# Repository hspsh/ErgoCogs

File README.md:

# ErgoCogs - modular ErgoDox for lifelong tinkerers

The idea for this project was born, when a couple of us couldn't decide on which features should our upcoming ErgoDox fork have.

The (conflicting) ideas were:
* Basic teensy with mini-usb
* Anything USB-C based
* Battery - powered bluetooth keyboard
* Custom STM32-based logic with SMD pre-assembly at factory

So why not have it all? The simplest solution is splitting the design into 2 parts. It has many advantages:

* The stupid matrix PCB is also the most expensive, as PCB manufacturers usually charge extra for anything larger than 10x10cm.
* If you get bored with with your basic bitch cherry mx matrix, why not swap it for them crunchy jade kalihs? Maybe just for a weekend? Or maybe sell your old matrix to a fellow hacker!
* The controller PCBs are small, and hence dirt cheap, and this is where most of customisation would take place. Take your time and experiment with wacky knobs and OLED displays until you get your perfect hackertyper experience.

It also has some disadvantages:

* The goldpin connector might be not the most relaiable way to connect 2PCBs. We're yet to check if this concept actually works out. Worst case, both sides may be semi-permanently soldered together with longer pinheaders.

## MatrixCog

This PCB is as dumb as it gets - it's basically an switch matrix routed do the 2x5 + 2x3 goldpin side connectors. It also features some LEDs.

To save some time, I recommend ordering this one with silicon diodes pre-assembled (`.cpl` file is included)

## BrainCogs

Here's when the fun begins. We provide 2 example hemispheres that feature some basic functionalities. You can fork the shit out of this repo and modify these for your own needs.

## Some pictures

More to come...

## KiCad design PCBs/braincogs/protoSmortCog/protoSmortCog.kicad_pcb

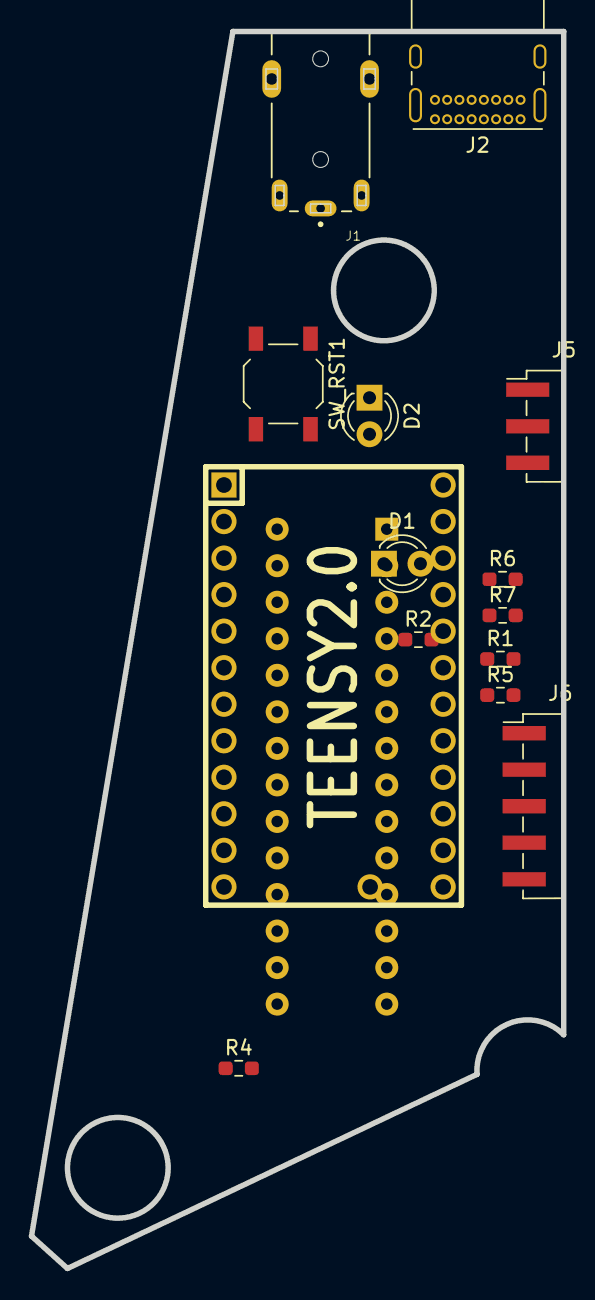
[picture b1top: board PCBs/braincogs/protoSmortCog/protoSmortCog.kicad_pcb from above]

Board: 2 copper layers, 37.0 x 86.0 mm, 15 parts (1 on the bottom side), 28 nets, no tracks yet.

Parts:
D1, D2: LED; LED_D3.0mm_Clear
J1: AudioJack4; CLIFF_FC68125
J2: USB_C_Receptacle_USB2.0; USB_C_Receptacle_GCT_USB4085
J5: Conn_01x06; ErgoCogs_sidecon_brain_top
J6: Conn_01x10; ErgoCogs_sidecon_brain_bot
R1, R2, R4, R5, R6, R7: 4k7; R_0603_1608Metric_Pad0.98x0.95mm_HandSolder
SW_RST1: SWITCH_PUSH; SW_SPST_TL3342
U1: TEENSY2.0; TEENSY_2.0_WITH_RESET
U2: MCP23018; DIP-28_W7.62mm

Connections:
/COL0_13: J6.10, U2.20
/COL1_12: J6.9, U2.21
/COL2_11: J6.8, U2.22
/COL3_10: J6.7, U2.23
/COL4_9: J6.6, U2.24
/COL5_8: J6.5, U2.25
/COL6_7: J6.4, U2.26
/LED_A: R1.1, U1.21, U2.10
/LED_B: R2.1, U1.22, U2.9
/LED_GPIO: J6.2, U1.6
/ROW0: J5.1, U1.23, U2.8
/ROW1: J5.2, U1.24, U2.7
/ROW2: J5.3, U1.25, U2.6
/ROW3: J5.4, U1.26, U2.5
/ROW4: J5.5, U1.27, U2.4
/ROW5: J5.6, U1.28, U2.3
/RST: SW_RST1.1, U1.16
/SCL: J1.R1, R4.2, U1.7, U2.12
/SDA: J1.T, R5.2, U1.8, U2.13
GND: D1.1, D2.1, J1.S, J2.A1, J2.A12, J2.B1, J2.B12, J2.S1, J6.3, R6.2, R7.2, SW_RST1.2, U1.1, U1.18, U2.1, U2.15
unnamed: D1.2, R1.2
unnamed: D2.2, R2.2
unnamed: J2.A5, R6.1
unnamed: J2.A6, J2.B6
unnamed: J2.A7, J2.B7
unnamed: J2.B5, R7.1
VBUS: J2.A4, J2.A9, J2.B4, J2.B9
VCC: J1.R2, J6.1, R4.1, R5.1, U1.20, U1.29, U2.11, U2.16

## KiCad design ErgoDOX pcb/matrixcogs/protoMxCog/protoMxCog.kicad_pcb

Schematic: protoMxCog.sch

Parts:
D1, D4: WS2812B; LED_WS2812B_PLCC4_5.0x5.0mm_P3.2mm
D1:7, D1:8: D; DIODE
D2, D3: LED_R; LED_0805_2012Metric_Pad1.15x1.40mm_HandSolder
D5, D6: LED_G; LED_0805_2012Metric_Pad1.15x1.40mm_HandSolder
H99: MECHANICAL; ErgoDOXmech
J1: Conn_01x06; ErgoCogs_sidecon_top
J2: Conn_01x10; ErgoCogs_sidecon_bot
R1, R2, R3, R4: 470; R_0603_1608Metric_Pad0.98x0.95mm_HandSolder
S1, S2: STAB200; STAB_PCB940
SW0:7: SW0:6; MX_FLIP_DIODE
SW0:8: SW0:5; MX_FLIP_DIODE
SW0:9: SW0:4; MX_FLIP_DIODE
SW0:10: SW0:3; MX_FLIP_DIODE
SW0:11: SW0:2; MX_FLIP_DIODE
SW0:12: SW0:1; MX_FLIP_DIODE
SW1:9: SW1:4; MX_FLIP_DIODE
SW1:10: SW1:3; MX_FLIP_DIODE
SW1:11: SW1:2; MX_FLIP_DIODE
SW1:12: SW1:1; MX_FLIP_DIODE
SW1:13: SW1:0; MX_FLIP_DIODE
SW2:7: SW2:6; MX_FLIP_DIODE
SW2:8: SW2:5; MX_FLIP_DIODE
SW2:9: SW2:4; MX_FLIP_DIODE
SW2:10: SW2:3; MX_FLIP_DIODE
SW2:11: SW2:2; MX_FLIP_DIODE
SW2:12: SW2:1; MX_FLIP_DIODE
SW2:13: SW2:0; MX_FLIP_DIODE
SW3:8: SW3:5; MX_FLIP_DIODE
SW3:9: SW3:4; MX_FLIP_DIODE
SW3:10: SW3:3; MX_FLIP_DIODE
SW3:11: SW3:2; MX_FLIP_DIODE
SW3:12: SW3:1; MX_FLIP_DIODE
SW3:13: SW3:0; MX_FLIP_DIODE
SW4:7: SW4:6; MX_FLIP_DIODE
SW4:8: SW4:5; MX_FLIP_DIODE
SW4:9: SW4:4; MX_FLIP_DIODE
SW4:10: SW4:3; MX_FLIP_DIODE
SW4:11: SW4:2; MX_FLIP_DIODE
SW4:12: SW4:1; MX_FLIP_DIODE
SW4:13: SW4:0; MX_FLIP_DIODE
SW5:7: SW5:6; MX_FLIP_DIODE
SW5:8: SW5:5; MX_FLIP_DIODE
SW5:9: SW5:4; MX_FLIP_DIODE
SW5:10: SW5:3; MX_FLIP_DIODE
SW5:11: SW5:2; MX_FLIP_DIODE
SW5:12: SW5:1; MX_FLIP_DIODE
SW5:13: SW5:0; MX_FLIP_DIODE
SX0:10: SX0:3; MX_FLIP
SX0:11: SX0:2; MX_FLIP
SX1:7: SX1:6; MX_FLIP
SX1:8: SX1:5; MX_FLIP

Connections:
/COL0_13: J2.10, SW1:13.4, SW2:13.4, SW3:13.4, SW4:13.4, SW5:13.4
/COL1_12: J2.9, SW0:12.4, SW1:12.4, SW2:12.4, SW3:12.4, SW4:12.4, SW5:12.4
/COL2_11: J2.8, SW0:11.4, SW1:11.4, SW2:11.4, SW3:11.4, SW4:11.4, SW5:11.4
/COL3_10: J2.7, SW0:10.4, SW1:10.4, SW2:10.4, SW3:10.4, SW4:10.4, SW5:10.4
/COL4_9: J2.6, SW0:9.4, SW1:9.4, SW2:9.4, SW3:9.4, SW4:9.4, SW5:9.4
/COL5_8: D1:8.2, J2.5, SW0:8.4, SW2:8.4, SW3:8.4, SW4:8.4, SW5:8.4
/COL6_7: D1:7.2, J2.4, SW0:7.4, SW2:7.4, SW4:7.4, SW5:7.4
/LED_GPIO: D1.4, D4.4, J2.2, R2.1, R4.1
/ROW0: J1.1, SW0:7.1, SW0:8.1, SW0:9.1, SW0:10.1, SW0:11.1, SW0:12.1, SX0:10.1, SX0:11.1
/ROW1: J1.2, SW1:9.1, SW1:10.1, SW1:11.1, SW1:12.1, SW1:13.1, SX1:7.1, SX1:8.1
/ROW2: J1.3, SW2:7.1, SW2:8.1, SW2:9.1, SW2:10.1, SW2:11.1, SW2:12.1, SW2:13.1
/ROW3: J1.4, SW3:8.1, SW3:9.1, SW3:10.1, SW3:11.1, SW3:12.1, SW3:13.1
/ROW4: J1.5, SW4:7.1, SW4:8.1, SW4:9.1, SW4:10.1, SW4:11.1, SW4:12.1, SW4:13.1
/ROW5: J1.6, SW5:7.1, SW5:8.1, SW5:9.1, SW5:10.1, SW5:11.1, SW5:12.1, SW5:13.1
GND: D1.3, D2.2, D3.2, D4.3, D5.2, D6.2, J2.3, SW0:7.0, SW0:8.0, SW0:9.0, SW0:10.0, SW0:11.0, SW0:12.0, SW1:9.0, SW1:10.0, SW1:11.0, SW1:12.0, SW1:13.0, SW2:7.0, SW2:8.0, SW2:9.0, SW2:10.0, SW2:11.0, SW2:12.0, SW2:13.0, SW3:8.0, SW3:9.0, SW3:10.0, SW3:11.0, SW3:12.0, SW3:13.0, SW4:7.0, SW4:8.0, SW4:9.0, SW4:10.0, SW4:11.0, SW4:12.0, SW4:13.0, SW5:7.0, SW5:8.0, SW5:9.0, SW5:10.0, SW5:11.0, SW5:12.0, SW5:13.0
unnamed: D1:7.1, SX1:7.2
unnamed: D1:8.1, SX1:8.2
unnamed: D2.1, R1.2
unnamed: D3.1, R3.2
unnamed: D5.1, R2.2
unnamed: D6.1, R4.2
unnamed: SW0:7.2, SW0:7.3
unnamed: SW0:8.2, SW0:8.3
unnamed: SW0:9.2, SW0:9.3
unnamed: SW0:10.2, SW0:10.3, SX0:10.2
unnamed: SW0:11.2, SW0:11.3, SX0:11.2
unnamed: SW0:12.2, SW0:12.3
unnamed: SW1:9.2, SW1:9.3
unnamed: SW1:10.2, SW1:10.3
unnamed: SW1:11.2, SW1:11.3
unnamed: SW1:12.2, SW1:12.3
unnamed: SW1:13.2, SW1:13.3
unnamed: SW2:7.2, SW2:7.3
unnamed: SW2:8.2, SW2:8.3
unnamed: SW2:9.2, SW2:9.3
unnamed: SW2:10.2, SW2:10.3
unnamed: SW2:11.2, SW2:11.3
unnamed: SW2:12.2, SW2:12.3
unnamed: SW2:13.2, SW2:13.3
unnamed: SW3:8.2, SW3:8.3
unnamed: SW3:9.2, SW3:9.3
unnamed: SW3:10.2, SW3:10.3
unnamed: SW3:11.2, SW3:11.3
unnamed: SW3:12.2, SW3:12.3
unnamed: SW3:13.2, SW3:13.3
unnamed: SW4:7.2, SW4:7.3
unnamed: SW4:8.2, SW4:8.3
unnamed: SW4:9.2, SW4:9.3
unnamed: SW4:10.2, SW4:10.3
unnamed: SW4:11.2, SW4:11.3
unnamed: SW4:12.2, SW4:12.3
unnamed: SW4:13.2, SW4:13.3
unnamed: SW5:7.2, SW5:7.3
unnamed: SW5:8.2, SW5:8.3
unnamed: SW5:9.2, SW5:9.3
unnamed: SW5:10.2, SW5:10.3
unnamed: SW5:11.2, SW5:11.3
unnamed: SW5:12.2, SW5:12.3
unnamed: SW5:13.2, SW5:13.3
VCC: D1.1, D4.1, J2.1, R1.1, R3.1

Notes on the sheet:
TOP
BOT

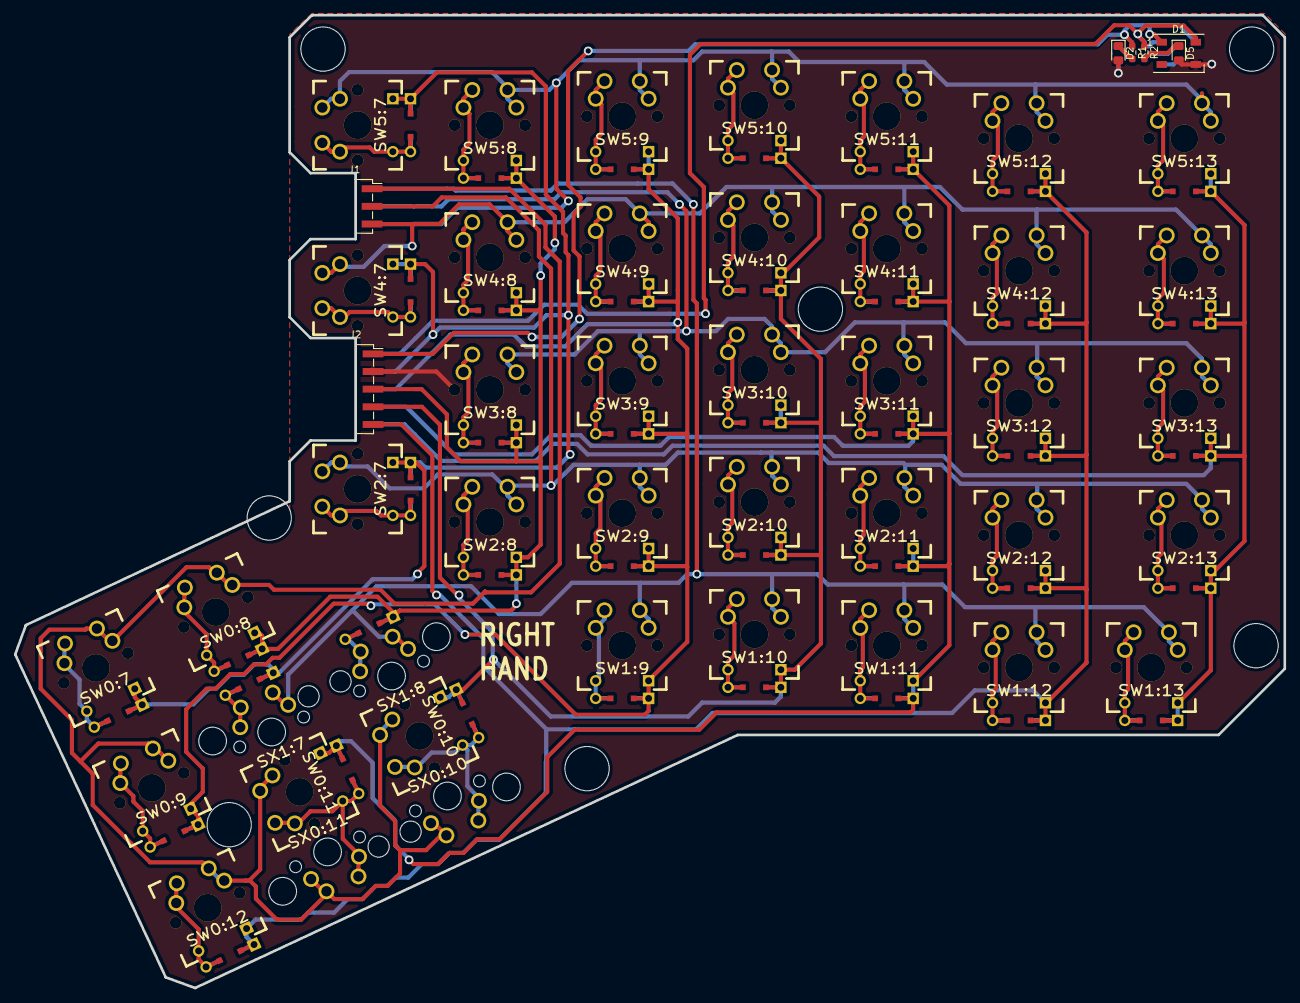
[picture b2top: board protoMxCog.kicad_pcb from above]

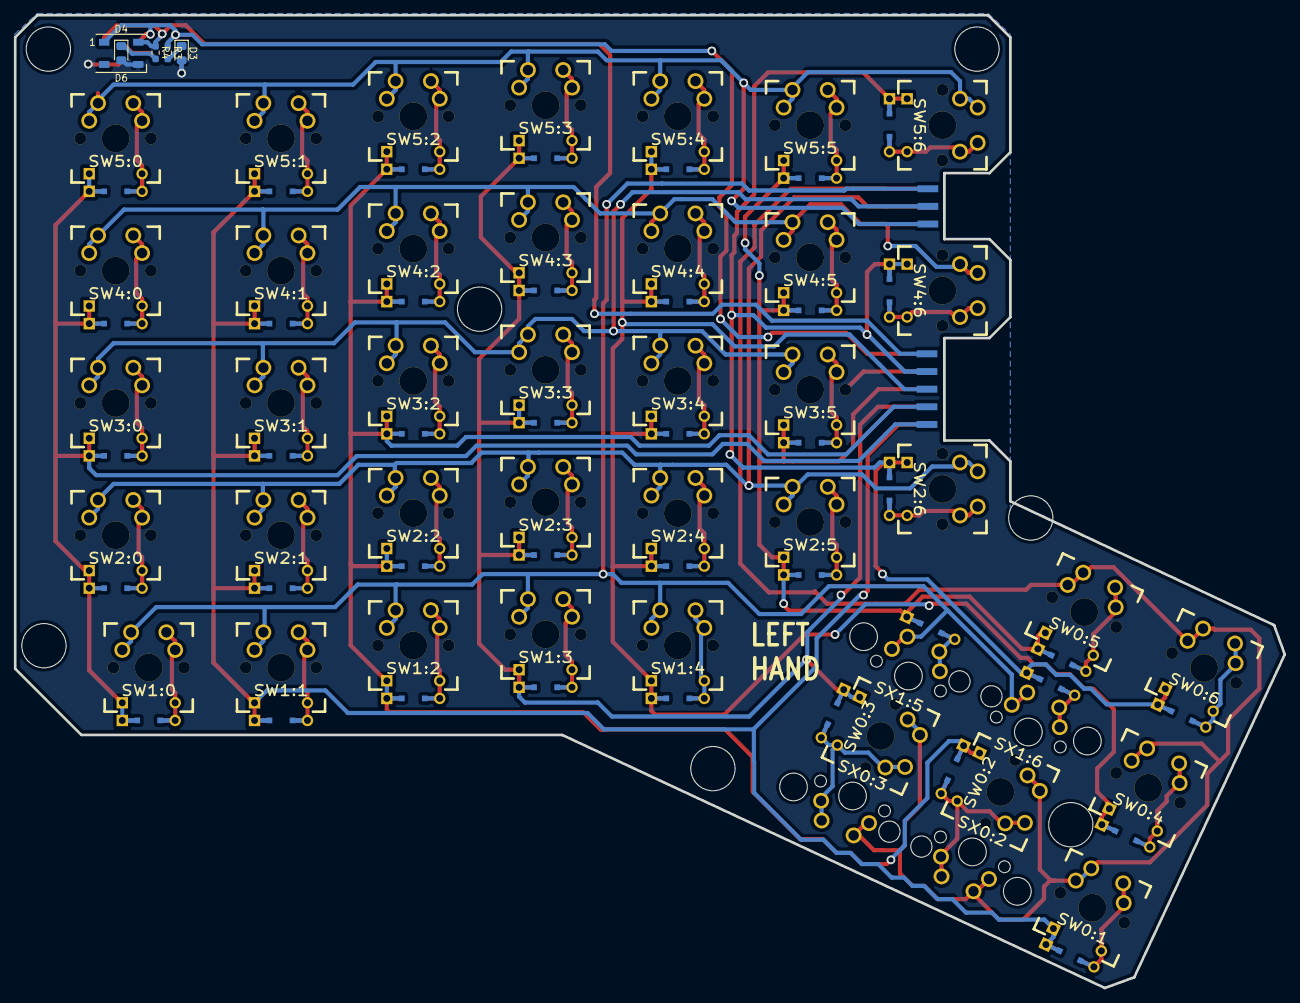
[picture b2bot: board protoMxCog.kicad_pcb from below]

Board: 2 copper layers, 182.8 x 140.1 mm, 59 parts (5 on the bottom side), 60 nets.

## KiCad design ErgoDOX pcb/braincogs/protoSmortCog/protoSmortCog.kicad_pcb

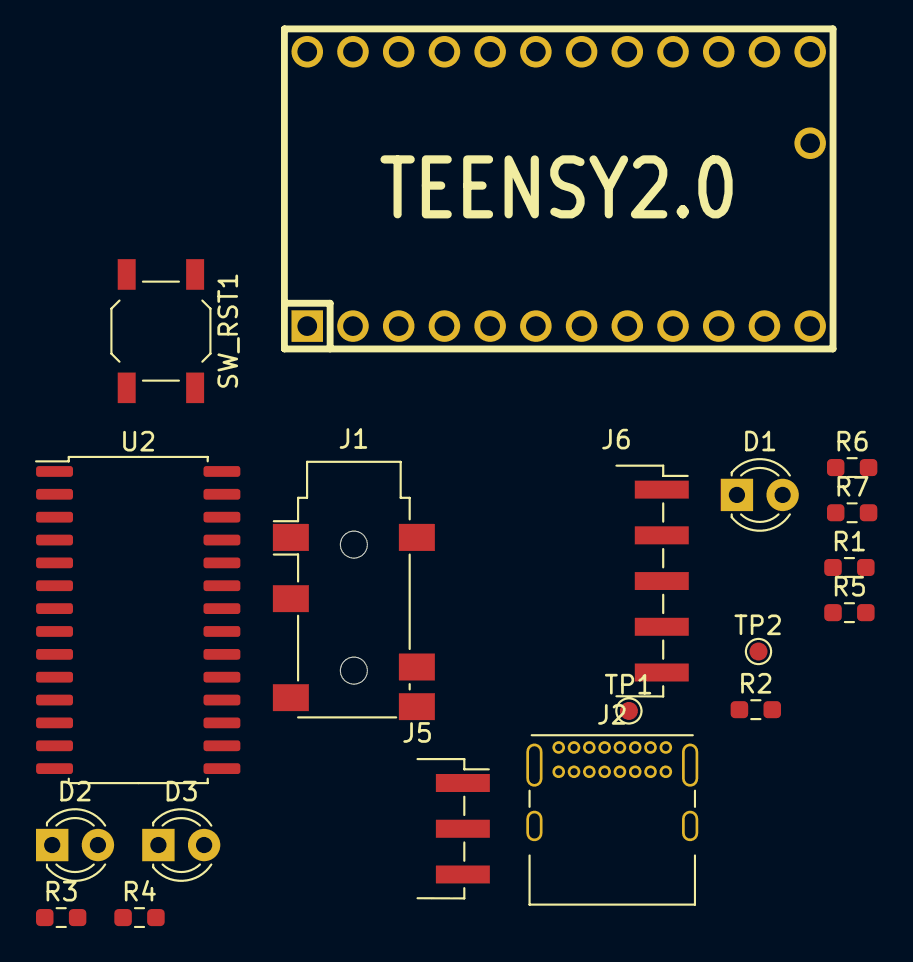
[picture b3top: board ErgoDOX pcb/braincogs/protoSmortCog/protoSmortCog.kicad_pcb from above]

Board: 2 copper layers, 19 parts (0 on the bottom side), 29 nets, no tracks yet.

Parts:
D1, D2, D3: LED; LED_D3.0mm_Clear
J1: AudioJack4_SwitchTR1; Jack_3.5mm_PJ311_Horizontal
J2: USB_C_Receptacle_USB2.0; USB_C_Receptacle_GCT_USB4085
J5: Conn_01x06; ErgoCogs_sidecon_top
J6: Conn_01x10; ErgoCogs_sidecon_bot
R1, R2, R3, R4, R5, R6, R7: 4k7; R_0603_1608Metric_Pad0.98x0.95mm_HandSolder
SW_RST1: SWITCH_PUSH; SW_SPST_TL3342
TP1, TP2: TestPoint_Small; TestPoint_Pad_D1.0mm
U1: TEENSY2.0; TEENSY_2.0_WITH_RESET
U2: MCP23017_SO; SOIC-28W_7.5x17.9mm_P1.27mm

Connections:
/COL0: J6.10, U2.21
/COL1: J6.9, U2.22
/COL2: J6.8, U2.23
/COL3: J6.7, U2.24
/COL4: J6.6, U2.25
/COL5: J6.5, U2.26
/COL6: J6.4, U2.27
/LED_A: R1.1, U1.21, U2.8
/LED_B: R2.1, U1.22, U2.7
/LED_C: R3.1, U1.6
/ROW0: J5.6, U1.23, U2.6
/ROW1: J5.5, U1.24, U2.5
/ROW2: J5.4, U1.25, U2.4
/ROW3: J5.3, U1.26, U2.3
/ROW4: J5.2, U1.27, U2.2
/ROW5: J5.1, U1.28, U2.1
/RST: SW_RST1.1, U1.16
/SCL: R4.2, U1.7, U2.12, U2.13
/SDA: R5.2, U1.8
GND: D1.1, D2.1, D3.1, J2.A1, J2.A12, J2.B1, J2.B12, J2.S1, J6.3, R6.2, R7.2, SW_RST1.2, U1.1, U1.18, U2.10
unnamed: D1.2, R1.2
unnamed: D2.2, R2.2
unnamed: D3.2, R3.2
unnamed: J2.A5, R6.1
unnamed: J2.A6, J2.B6, TP2.1
unnamed: J2.A7, J2.B7, TP1.1
unnamed: J2.B5, R7.1
VBUS: J2.A4, J2.A9, J2.B4, J2.B9
VCC: J6.1, R4.1, R5.1, U1.20, U1.29, U2.18

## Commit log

2021-02-15 adding cringe
2021-02-15 uncscronching the original repo state
2021-02-15 Creating proper directory structure, splitting pcb project into 2 independent projects
2021-02-15 removing original project files
2021-02-23 removing top part of PCB on switch matrix board
2021-03-16 refactoring library structure, finishing basic matrix cog
2021-03-21 renaming projects
2021-03-21 adjusting former ergodox project for a smart cog template (WIP)
2021-04-23 1st version of braincogs
2021-06-02 repo cleanup, adding fab files for PCBs
2021-06-02 removing spaces from folder names, adding example photo
2021-06-02 adding some pictures
2021-06-09 Switch mount plate
2021-06-09 gitignore LibreCAD temp files
2021-06-14 Case alpha
2021-06-15 Some adjustments: moar rails, some pictures, 12mm height for M2x12 screws
2021-10-20 Yeeee
2022-01-31 Add license
